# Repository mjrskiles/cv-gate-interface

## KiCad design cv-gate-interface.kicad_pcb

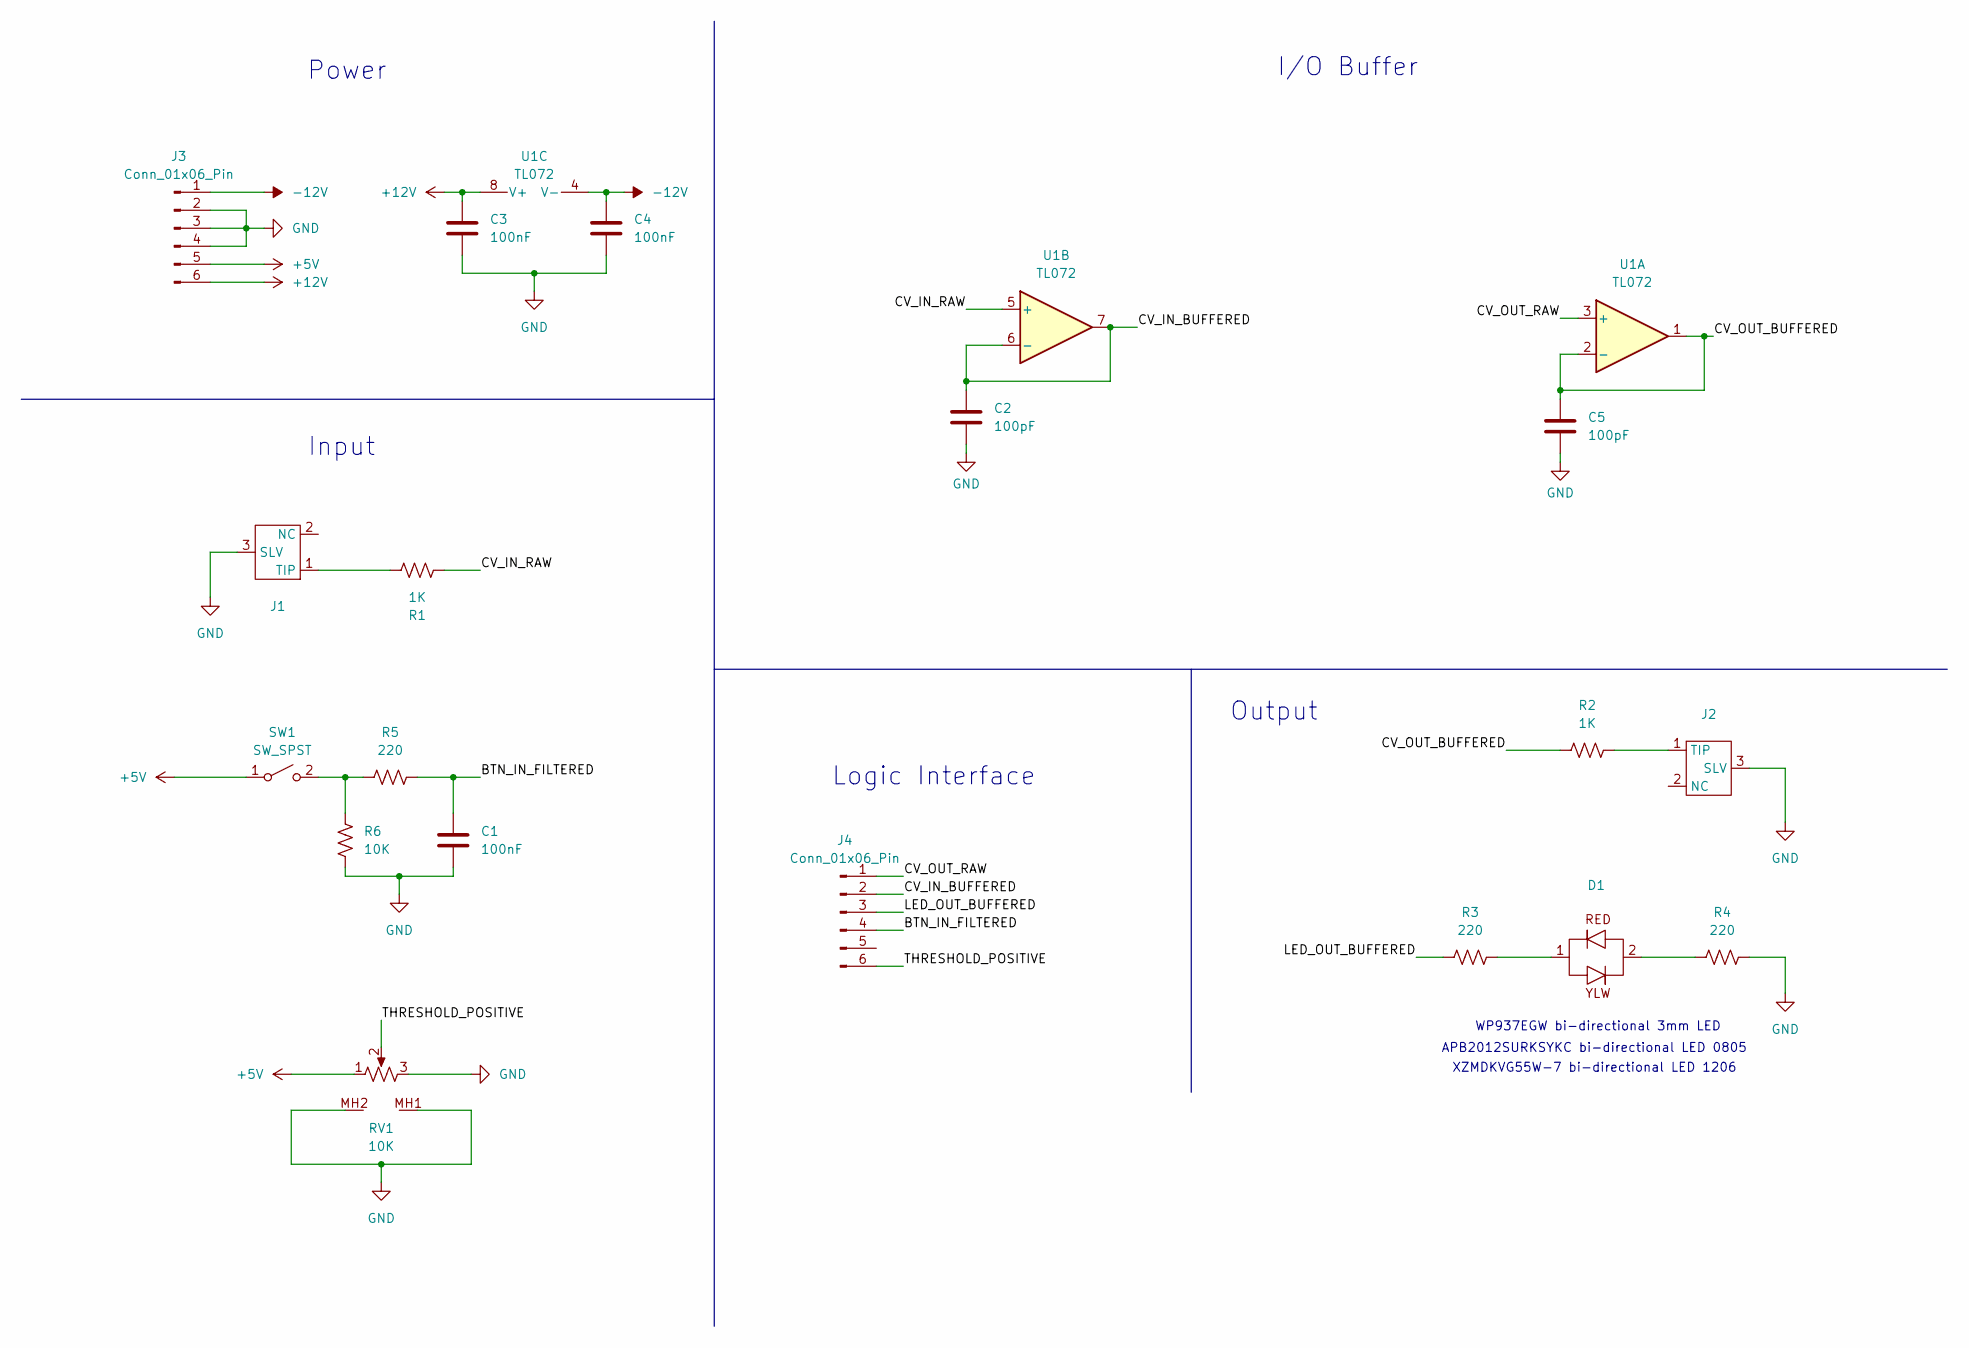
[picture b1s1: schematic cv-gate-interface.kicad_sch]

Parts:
C1, C3, C4: 100nF; C_0805_2012Metric_Pad1.18x1.45mm_HandSolder
C2, C5: 100pF; C_0805_2012Metric_Pad1.18x1.45mm_HandSolder
D1: XZMDKVG55W-7
J1, J2: THONKICONN
J3, J4: Conn_01x06_Pin; PinHeader_1x06_P1.27mm_Vertical
R1, R2: 1K; R_0805_2012Metric_Pad1.20x1.40mm_HandSolder
R3, R4, R5: 220; R_0805_2012Metric_Pad1.20x1.40mm_HandSolder
R6: 10K; R_0805_2012Metric_Pad1.20x1.40mm_HandSolder
RV1: 10K; PTV09A-4020F-B102
SW1: SW_SPST; SWITCH_SPST_6mm_BUTTON_PTH
U1: TL072; SOIC-8_3.9x4.9mm_P1.27mm

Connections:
+5V: J3.5, RV1.1, SW1.1 (A)
+12V: C3.1, J3.6, U1.8 (V+)
-12V: C4.1, J3.1, U1.4 (V-)
/BTN_IN_FILTERED: C1.1, J4.4, R5.2
/CV_IN_BUFFERED: C2.1, J4.2, U1.6 (-), U1.7
/CV_IN_RAW: R1.1, U1.5 (+)
/CV_OUT_BUFFERED: C5.1, R2.1, U1.1, U1.2 (-)
/CV_OUT_RAW: J4.1, U1.3 (+)
/LED_OUT_BUFFERED: J4.3, R3.1
/THRESHOLD_POSITIVE: J4.6, RV1.2
GND: C1.2, C2.2, C3.2, C4.2, C5.2, J1.3 (SLV), J2.3 (SLV), J3.2, J3.3, J3.4, R4.2, R6.1, RV1.3, RV1.MH1 (GND), RV1.MH2 (GND)
unnamed: D1.1, R3.2
unnamed: D1.2, R4.1
unnamed: J1.1 (TIP), R1.2
unnamed: J2.1 (TIP), R2.2
unnamed: R5.1, R6.2, SW1.2 (B)

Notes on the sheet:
Output
I/O Buffer
Power
APB2012SURKSYKC bi-directional LED 0805
Input
XZMDKVG55W-7 bi-directional LED 1206
WP937EGW bi-directional 3mm LED
Logic Interface

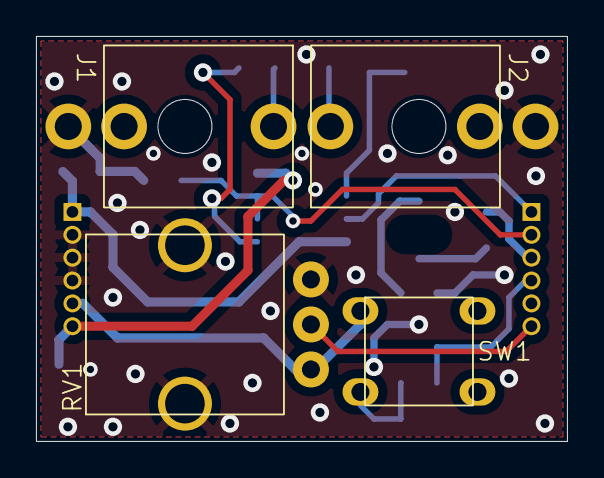
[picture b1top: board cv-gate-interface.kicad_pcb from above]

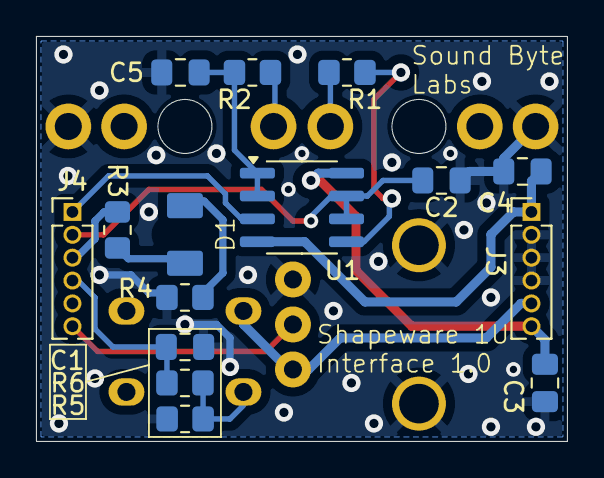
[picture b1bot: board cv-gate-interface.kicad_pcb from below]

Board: 2 copper layers, 29.5 x 22.5 mm, 19 parts (15 on the bottom side), 16 nets.

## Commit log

2025-03-10 Changed pot to 10K, fixed routing
